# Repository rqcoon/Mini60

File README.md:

# Mini60
I don't know what this board is but it's a board for sure

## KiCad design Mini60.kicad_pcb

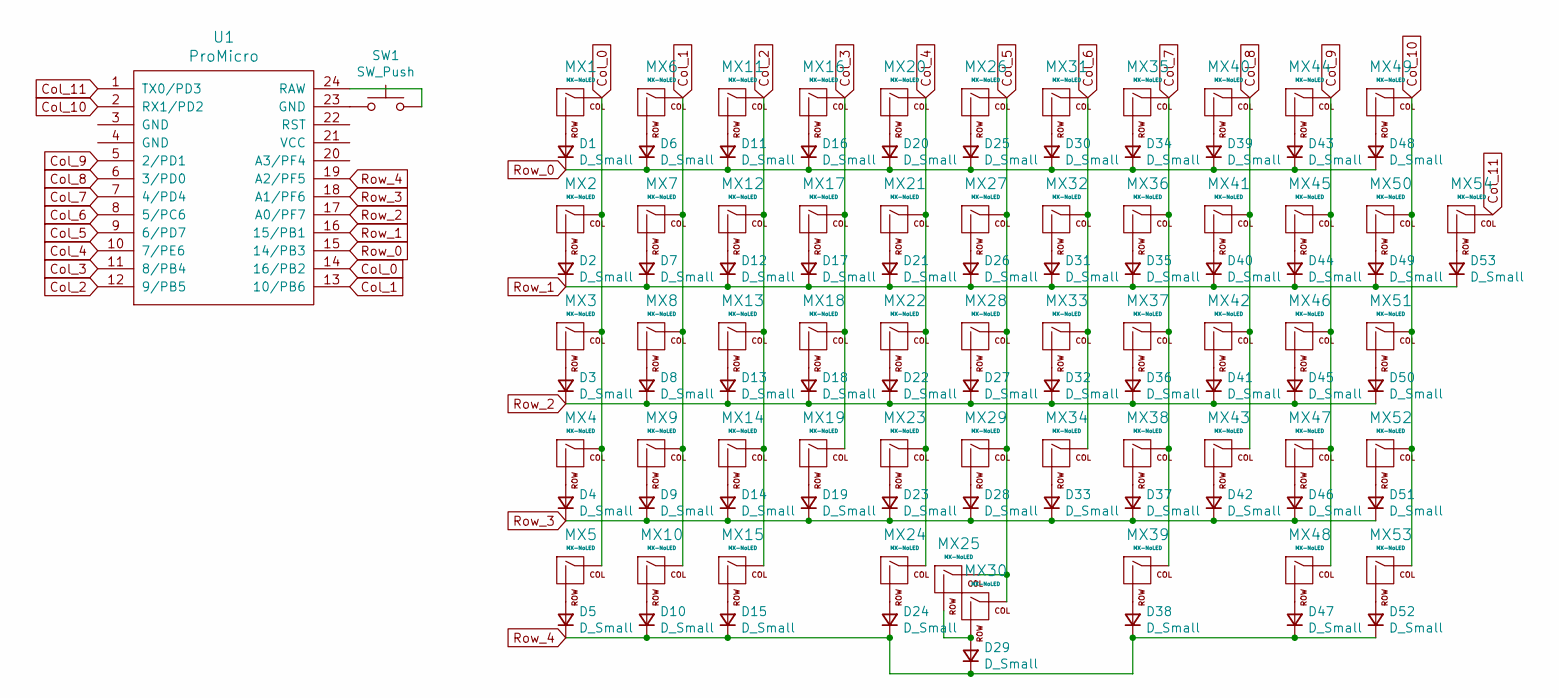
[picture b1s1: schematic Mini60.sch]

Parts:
D1, D2, D3, D4, D5, D6, D7, D8, D9, D10, D11, D12, D13, D14, D15, D16, D17, D18, D19, D20, D21, D22, D23, D24, D25, D26, D27, D28, D29, D30, D31, D32, D33, D34, D35, D36, D37, D38, D39, D40, D41, D42, D43, D44, D45, D46, D47, D48, D49, D50, D51, D52, D53: D_Small; Diode-dual
MX1, MX2, MX5, MX6, MX7, MX8, MX9, MX11, MX12, MX13, MX14, MX15, MX16, MX17, MX18, MX19, MX20, MX21, MX22, MX23, MX26, MX27, MX28, MX29, MX31, MX32, MX33, MX34, MX35, MX36, MX37, MX38, MX40, MX41, MX42, MX43, MX44, MX45, MX46, MX47, MX50, MX54: MX-NoLED; MXOnly-1U-NoLED
MX3, MX10, MX30, MX48, MX53: MX-NoLED; MXOnly-1.25U-NoLED
MX4, MX49, MX52: MX-NoLED; MXOnly-1.5U-NoLED
MX24: MX-NoLED; MXOnly-2.75U-ReversedStabilizers-NoLED
MX25: MX-NoLED; MXOnly-6.25U-ReversedStabilizers-NoLED
MX39: MX-NoLED; MXOnly-2.25U-ReversedStabilizers-NoLED
MX51: MX-NoLED; MXOnly-1.75U-NoLED
SW1: SW_Push; SW_SPST_SKQG_WithStem
U1: ProMicro; ArduinoProMicro

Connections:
Col_0: MX1.1 (COL), MX2.1 (COL), MX3.1 (COL), MX4.1 (COL), MX5.1 (COL), U1.14 (16/PB2)
Col_1: MX6.1 (COL), MX7.1 (COL), MX8.1 (COL), MX9.1 (COL), MX10.1 (COL), U1.13 (10/PB6)
Col_2: MX11.1 (COL), MX12.1 (COL), MX13.1 (COL), MX14.1 (COL), MX15.1 (COL), U1.12 (9/PB5)
Col_3: MX16.1 (COL), MX17.1 (COL), MX18.1 (COL), MX19.1 (COL), U1.11 (8/PB4)
Col_4: MX20.1 (COL), MX21.1 (COL), MX22.1 (COL), MX23.1 (COL), MX24.1 (COL), U1.10 (7/PE6)
Col_5: MX25.1 (COL), MX26.1 (COL), MX27.1 (COL), MX28.1 (COL), MX29.1 (COL), MX30.1 (COL), U1.9 (6/PD7)
Col_6: MX31.1 (COL), MX32.1 (COL), MX33.1 (COL), MX34.1 (COL), U1.8 (5/PC6)
Col_7: MX35.1 (COL), MX36.1 (COL), MX37.1 (COL), MX38.1 (COL), MX39.1 (COL), U1.7 (4/PD4)
Col_8: MX40.1 (COL), MX41.1 (COL), MX42.1 (COL), MX43.1 (COL), U1.6 (3/PD0)
Col_9: MX44.1 (COL), MX45.1 (COL), MX46.1 (COL), MX47.1 (COL), MX48.1 (COL), U1.5 (2/PD1)
Col_10: MX49.1 (COL), MX50.1 (COL), MX51.1 (COL), MX52.1 (COL), MX53.1 (COL), U1.2 (RX1/PD2)
Col_11: MX54.1 (COL), U1.1 (TX0/PD3)
unnamed: D1.2 (A), MX1.2 (ROW)
unnamed: D2.2 (A), MX2.2 (ROW)
unnamed: D3.2 (A), MX3.2 (ROW)
unnamed: D4.2 (A), MX4.2 (ROW)
unnamed: D5.2 (A), MX5.2 (ROW)
unnamed: D6.2 (A), MX6.2 (ROW)
unnamed: D7.2 (A), MX7.2 (ROW)
unnamed: D8.2 (A), MX8.2 (ROW)
unnamed: D9.2 (A), MX9.2 (ROW)
unnamed: D10.2 (A), MX10.2 (ROW)
unnamed: D11.2 (A), MX11.2 (ROW)
unnamed: D12.2 (A), MX12.2 (ROW)
unnamed: D13.2 (A), MX13.2 (ROW)
unnamed: D14.2 (A), MX14.2 (ROW)
unnamed: D15.2 (A), MX15.2 (ROW)
unnamed: D16.2 (A), MX16.2 (ROW)
unnamed: D17.2 (A), MX17.2 (ROW)
unnamed: D18.2 (A), MX18.2 (ROW)
unnamed: D19.2 (A), MX19.2 (ROW)
unnamed: D20.2 (A), MX20.2 (ROW)
unnamed: D21.2 (A), MX21.2 (ROW)
unnamed: D22.2 (A), MX22.2 (ROW)
unnamed: D23.2 (A), MX23.2 (ROW)
unnamed: D24.2 (A), MX24.2 (ROW)
unnamed: D25.2 (A), MX26.2 (ROW)
unnamed: D26.2 (A), MX27.2 (ROW)
unnamed: D27.2 (A), MX28.2 (ROW)
unnamed: D28.2 (A), MX29.2 (ROW)
unnamed: D29.2 (A), MX25.2 (ROW), MX30.2 (ROW)
unnamed: D30.2 (A), MX31.2 (ROW)
unnamed: D31.2 (A), MX32.2 (ROW)
unnamed: D32.2 (A), MX33.2 (ROW)
unnamed: D33.2 (A), MX34.2 (ROW)
unnamed: D34.2 (A), MX35.2 (ROW)
unnamed: D35.2 (A), MX36.2 (ROW)
unnamed: D36.2 (A), MX37.2 (ROW)
unnamed: D37.2 (A), MX38.2 (ROW)
unnamed: D38.2 (A), MX39.2 (ROW)
unnamed: D39.2 (A), MX40.2 (ROW)
unnamed: D40.2 (A), MX41.2 (ROW)
unnamed: D41.2 (A), MX42.2 (ROW)
unnamed: D42.2 (A), MX43.2 (ROW)
unnamed: D43.2 (A), MX44.2 (ROW)
unnamed: D44.2 (A), MX45.2 (ROW)
unnamed: D45.2 (A), MX46.2 (ROW)
unnamed: D46.2 (A), MX47.2 (ROW)
unnamed: D47.2 (A), MX48.2 (ROW)
unnamed: D48.2 (A), MX49.2 (ROW)
unnamed: D49.2 (A), MX50.2 (ROW)
unnamed: D50.2 (A), MX51.2 (ROW)
unnamed: D51.2 (A), MX52.2 (ROW)
unnamed: D52.2 (A), MX53.2 (ROW)
unnamed: D53.2 (A), MX54.2 (ROW)
unnamed: SW1.1, U1.23 (GND)
unnamed: SW1.2, U1.24 (RAW)
Row_0: D1.1 (K), D6.1 (K), D11.1 (K), D16.1 (K), D20.1 (K), D25.1 (K), D30.1 (K), D34.1 (K), D39.1 (K), D43.1 (K), D48.1 (K), U1.15 (14/PB3)
Row_1: D2.1 (K), D7.1 (K), D12.1 (K), D17.1 (K), D21.1 (K), D26.1 (K), D31.1 (K), D35.1 (K), D40.1 (K), D44.1 (K), D49.1 (K), D53.1 (K), U1.16 (15/PB1)
Row_2: D3.1 (K), D8.1 (K), D13.1 (K), D18.1 (K), D22.1 (K), D27.1 (K), D32.1 (K), D36.1 (K), D41.1 (K), D45.1 (K), D50.1 (K), U1.17 (A0/PF7)
Row_3: D4.1 (K), D9.1 (K), D14.1 (K), D19.1 (K), D23.1 (K), D28.1 (K), D33.1 (K), D37.1 (K), D42.1 (K), D46.1 (K), D51.1 (K), U1.18 (A1/PF6)
Row_4: D5.1 (K), D10.1 (K), D15.1 (K), D24.1 (K), D29.1 (K), D38.1 (K), D47.1 (K), D52.1 (K), U1.19 (A2/PF5)

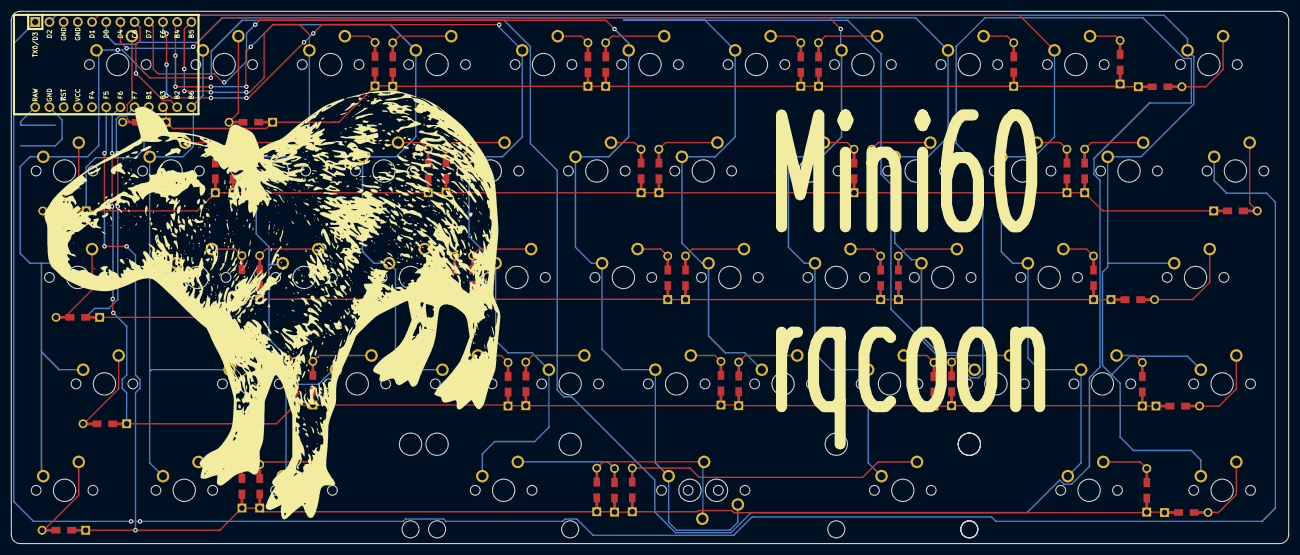
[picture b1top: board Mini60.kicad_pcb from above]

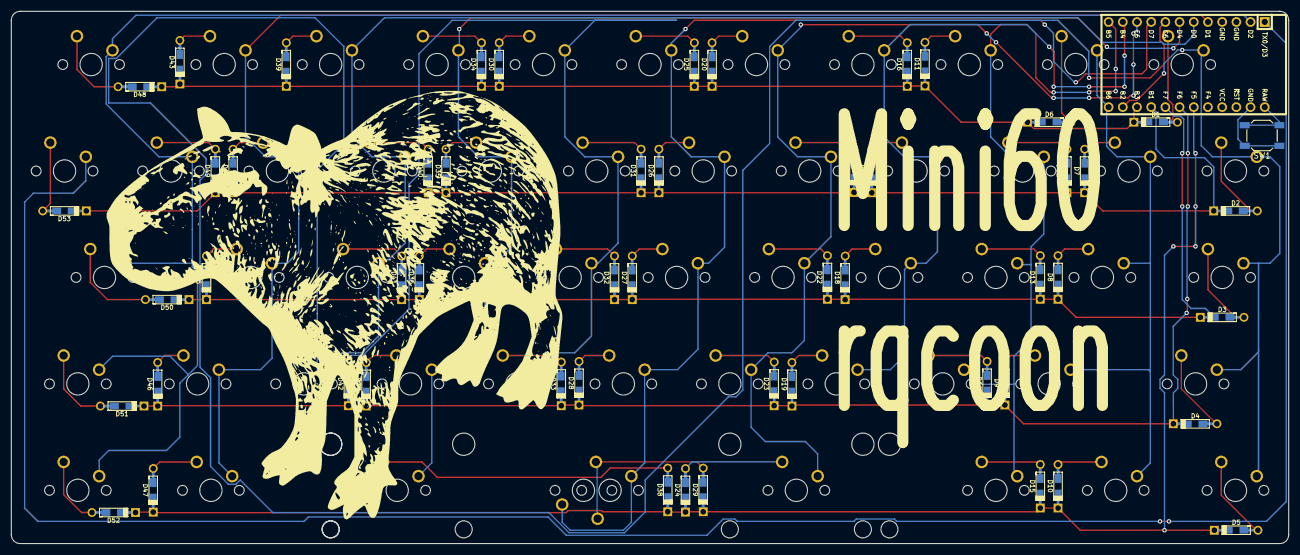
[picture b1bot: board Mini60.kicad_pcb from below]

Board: 2 copper layers, 228.6 x 95.3 mm, 109 parts (55 on the bottom side), 72 nets.

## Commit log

2021-12-08 Add Files
